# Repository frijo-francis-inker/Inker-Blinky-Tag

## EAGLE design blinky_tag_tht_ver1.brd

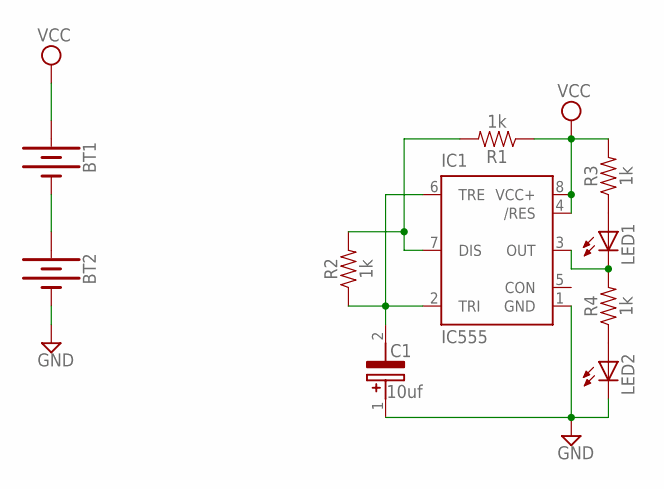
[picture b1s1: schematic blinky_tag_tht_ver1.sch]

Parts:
BT1, BT2: BATTERY-12MM_SMD; BATTCON_12MM
C1: 10uf; CAPPRD200W52D500H1250; MPN 100YXF10MEFC6.3X11
IC1: IC555; DIP08-KIT; MPN LM555CN
LED1, LED2: LED5MM
R1, R2, R3, R4: 1k; AXIAL-0.3

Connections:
GND: BT2.GND (-), C1.1 (+), IC1.1 (GND), LED2.K (C)
unnamed: BT1.GND (-), BT2.PWR@1 (+)
unnamed: IC1.7 (DIS), R1.P$2 (2), R2.P$2 (2)
unnamed: C1.2 (-), IC1.2 (TRI), IC1.6 (TRE), R2.P$1 (1)
unnamed: LED2.A, R4.P$1 (1)
unnamed: LED1.A, R3.P$1 (1)
unnamed: IC1.3 (OUT), LED1.K (C), R4.P$2 (2)
VCC: BT1.PWR@1 (+), IC1.4 (/RES), IC1.8 (VCC+), R1.P$1 (1), R3.P$2 (2)

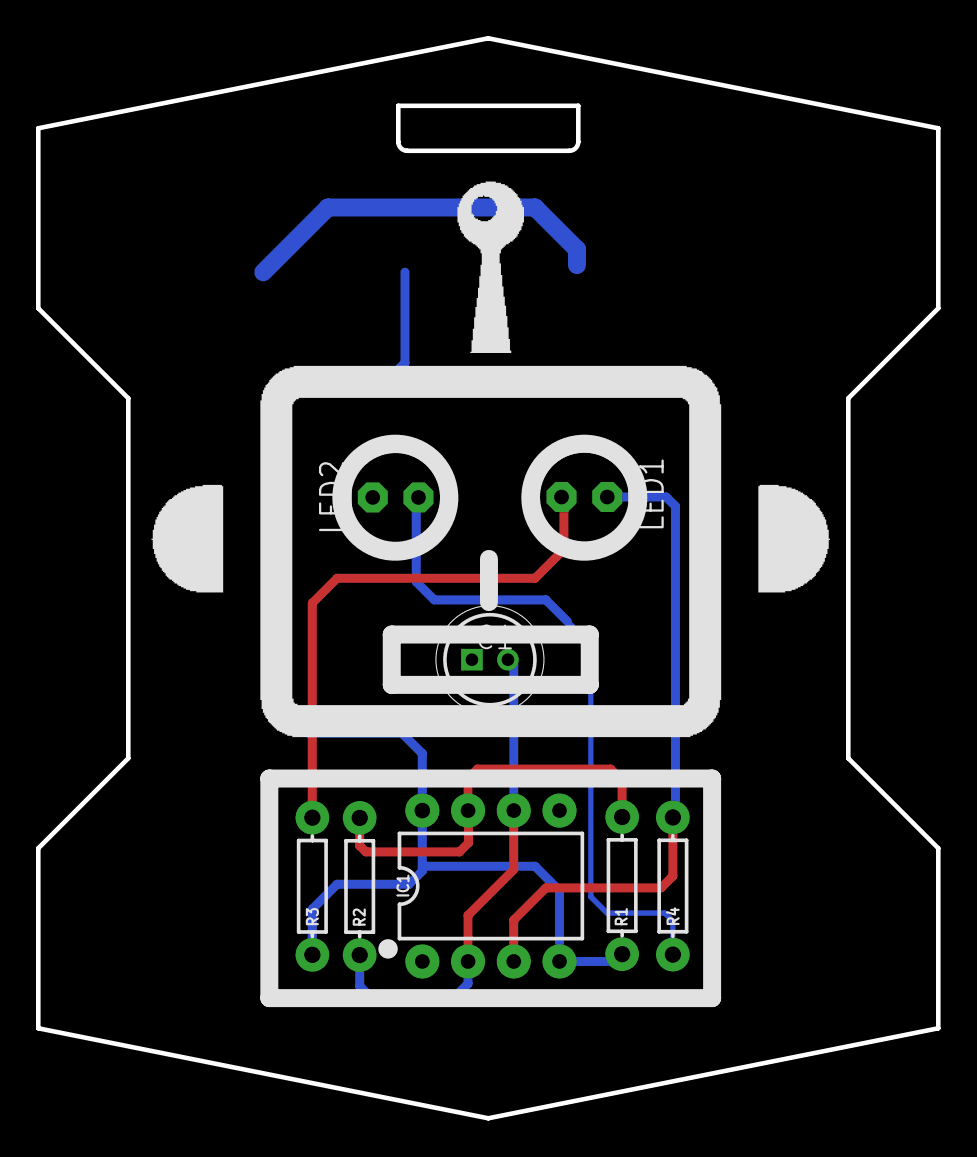
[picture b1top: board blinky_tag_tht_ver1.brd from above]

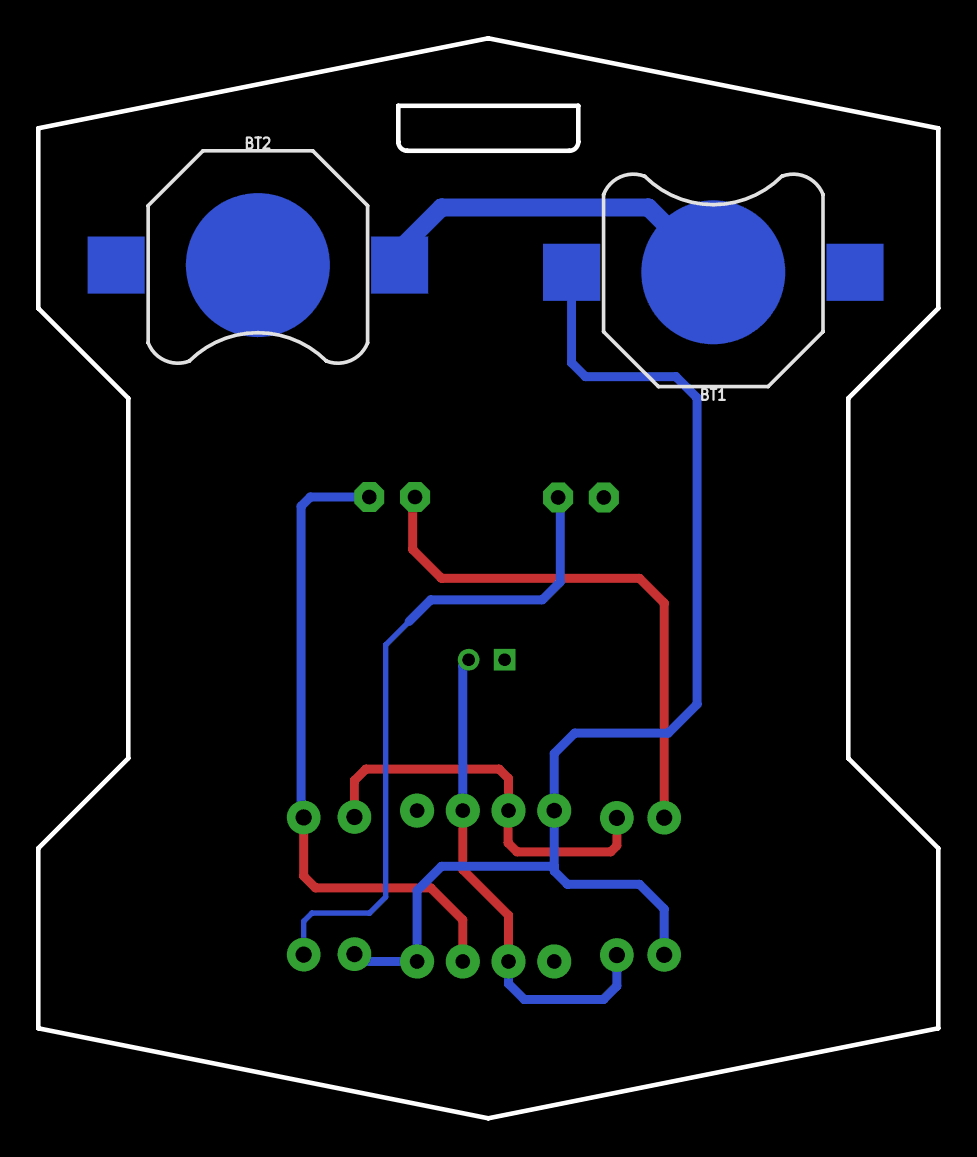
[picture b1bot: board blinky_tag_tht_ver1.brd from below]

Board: 2 copper layers, 50.0 x 60.0 mm, 11 parts (2 on the bottom side), 8 nets.

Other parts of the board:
U$1: ROBOT_2.8X_B

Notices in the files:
parts and their libraries:
SparkFun-Batteries: Licensing: Creative Commons ShareAlike 4.0 International - https://creativecommons.org/licenses/by-sa/4.0
